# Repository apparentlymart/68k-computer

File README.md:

This is intended to grow into a homebrew computer design based on the Freescale MC68SEC000 CPU.

However, it doesn't do anything yet.

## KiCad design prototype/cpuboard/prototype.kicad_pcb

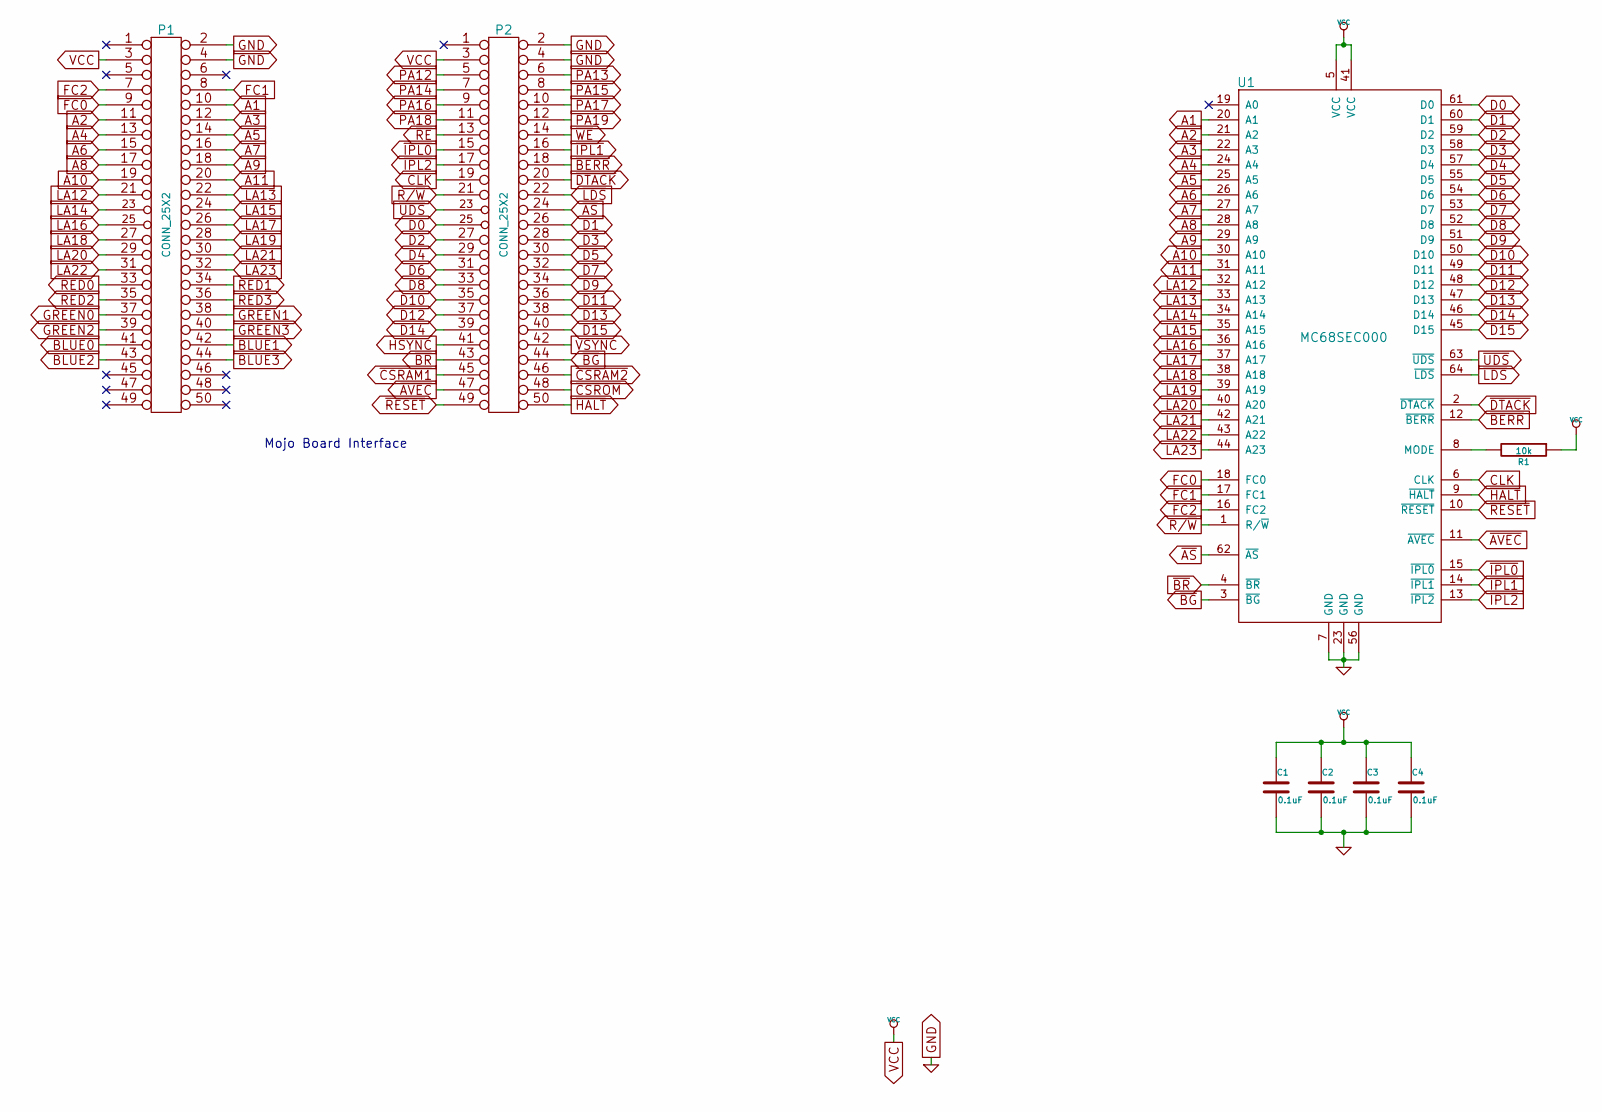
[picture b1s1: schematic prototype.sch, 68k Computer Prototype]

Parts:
C1, C2, C3, C4: 0.1uF; C_0805_HandSoldering
P1, P2: CONN_25X2; Pin_Header_Straight_2x25
R1: 10k; R_0805_HandSoldering
U1: MC68SEC000; LQFP-64_14x14mm_Pitch0.8mm

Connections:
A1: P1.10, U1.20 (A1)
A2: P1.11, U1.21 (A2)
A3: P1.12, U1.22 (A3)
A4: P1.13, U1.24 (A4)
A5: P1.14, U1.25 (A5)
A6: P1.15, U1.26 (A6)
A7: P1.16, U1.27 (A7)
A8: P1.17, U1.28 (A8)
A9: P1.18, U1.29 (A9)
A10: P1.19, U1.30 (A10)
A11: P1.20, U1.31 (A11)
BLUE0: P1.41
BLUE1: P1.42
BLUE2: P1.43
BLUE3: P1.44
CLK: P2.19, U1.6 (CLK)
D0: P2.25, U1.61 (D0)
D1: P2.26, U1.60 (D1)
D2: P2.27, U1.59 (D2)
D3: P2.28, U1.58 (D3)
D4: P2.29, U1.57 (D4)
D5: P2.30, U1.55 (D5)
D6: P2.31, U1.54 (D6)
D7: P2.32, U1.53 (D7)
D8: P2.33, U1.52 (D8)
D9: P2.34, U1.51 (D9)
D10: P2.35, U1.50 (D10)
D11: P2.36, U1.49 (D11)
D12: P2.37, U1.48 (D12)
D13: P2.38, U1.47 (D13)
D14: P2.39, U1.46 (D14)
D15: P2.40, U1.45 (D15)
FC0: P1.9, U1.18 (FC0)
FC1: P1.8, U1.17 (FC1)
FC2: P1.7, U1.16 (FC2)
GND: C1.2, C2.2, C3.2, C4.2, P1.2, P1.4, P2.2, P2.4, U1.7 (GND), U1.23 (GND), U1.56 (GND)
GREEN0: P1.37
GREEN1: P1.38
GREEN2: P1.39
GREEN3: P1.40
HSYNC: P2.41
LA12: P1.21, U1.32 (A12)
LA13: P1.22, U1.33 (A13)
LA14: P1.23, U1.34 (A14)
LA15: P1.24, U1.35 (A15)
LA16: P1.25, U1.36 (A16)
LA17: P1.26, U1.37 (A17)
LA18: P1.27, U1.38 (A18)
LA19: P1.28, U1.39 (A19)
LA20: P1.29, U1.40 (A20)
LA21: P1.30, U1.42 (A21)
LA22: P1.31, U1.43 (A22)
LA23: P1.32, U1.44 (A23)
unnamed: R1.2, U1.8 (MODE)
PA12: P2.5
PA13: P2.6
PA14: P2.7
PA15: P2.8
PA16: P2.9
PA17: P2.10
PA18: P2.11
PA19: P2.12
R/~W: P2.21, U1.1 (R/~W)
RED0: P1.33
RED1: P1.34
RED2: P1.35
RED3: P1.36
VCC: C1.1, C2.1, C3.1, C4.1, P1.3, P2.3, R1.1, U1.5 (VCC), U1.41 (VCC)
VSYNC: P2.42
~AS: P2.24, U1.62 (~AS)
~AVEC: P2.47, U1.11 (~AVEC)
~BERR: P2.18, U1.12 (~BERR)
~BG: P2.44, U1.3 (~BG)
~BR: P2.43, U1.4 (~BR)
~CSRAM1: P2.45
~CSRAM2: P2.46
~CSROM: P2.48
~DTACK: P2.20, U1.2 (~DTACK)
~HALT: P2.50, U1.9 (~HALT)
~IPL0: P2.15, U1.15 (~IPL0)
~IPL1: P2.16, U1.14 (~IPL1)
~IPL2: P2.17, U1.13 (~IPL2)
~LDS: P2.22, U1.64 (~LDS)
~RE: P2.13
~RESET: P2.49, U1.10 (~RESET)
~UDS: P2.23, U1.63 (~UDS)
~WE: P2.14

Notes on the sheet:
Mojo Board Interface

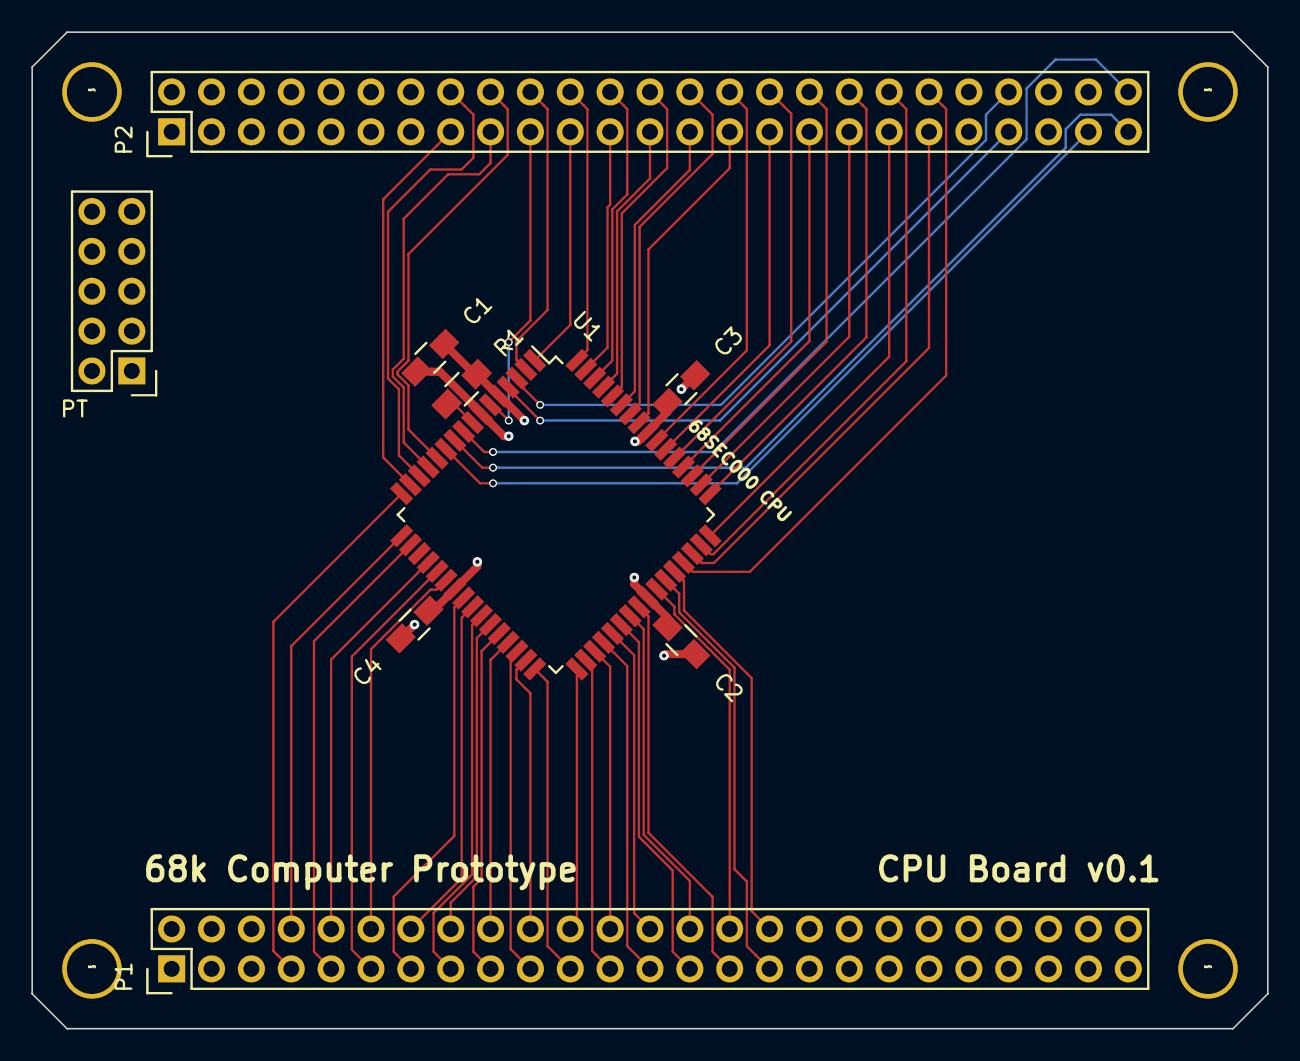
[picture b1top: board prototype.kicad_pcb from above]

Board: 4 copper layers, 78.7 x 63.5 mm, 13 parts (0 on the bottom side), 60 nets.

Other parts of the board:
MNT1, MNT2, MNT3, MNT4: HOLE
PT: Pin_Header_Straight_2x05

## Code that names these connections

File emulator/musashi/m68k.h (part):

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void m68k_modify_timeslice(int cycles); /* Modify cycles left */
void m68k_end_timeslice(void);          /* End timeslice now */

/* Set the IPL0-IPL2 pins on the CPU (IRQ).
 * A transition from < 7 to 7 will cause a non-maskable interrupt (NMI).
 * Setting IRQ to 0 will clear an interrupt request.
 */
void m68k_set_irq(unsigned int int_level);


/* Halt the CPU as if you pulsed the HALT pin. */
void m68k_pulse_halt(void);


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
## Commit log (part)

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2015-01-20 hi
    ____________________________________________________________
    / .--. /\
    / //V\/ _/ /\
    / '--' / \/
    / M C 6 8 0 0 0 /\/
    /___________________________________________________________/ /
2015-01-20 Yosys build script for the glue logic.
2015-01-20 Begin to factor the MMU out into a separate module.
2015-01-25 Simple RAM module to use in test benches.
    (For the real system we will use external RAM.)
2015-01-25 MMU mapping for user mode, via external page table RAM.
2015-01-25 New Makefile target to run Yosys-powered synthesis.
    Will probably want to also support the Xilinx proprietary tools later, but
    open source toolchain is fine for now while we're experimenting.
2015-01-25 Makefile targets to run test benches in Xilinx ISim.
    This is an alternative to using iverilog, which remains the primary way to
    run the test benches.
2015-01-25 Remove redundant begin/end in mmu.
2015-01-25 Show failing tests in prove output.
2015-01-25 Primary I/O Port mapping is actually implemented.
2015-01-25 Map Control, Page Table and Selectable Mappings in supervisor mode.
    This completes the basic MMU functionality.
2015-01-26 Factor out the TAP helpers so they can be used in all testbenches.
2015-02-08 A fake 68000 CPU implementing a 16-bit read cycle.
    This is intended to mock a 68000 CPU so that the memory/peripheral bus
    controller can more easily be tested. Only a 16-bit read cycle is
    implemented so far, but more to come.
2015-02-08 Support the Bus Error signal in fake68k reads.
    Bus Error makes the read cycle two clocks longer and allows the memory
    controller to halt processing until the bus error signal is un-asserted.
    The exception processing that would normally follow a bus error is not
    simulated, since that just entails a pair of standard read cycles to
    obtain the exception handler address.
2015-02-08 Makefile target xilinx_bitstream.
    Produces a bitstream file (.bin file) ready to be uploaded onto a
    Xilinx Spartan6 XC6SLX9 in a TQFP package.
    However, doesn't actually include a physical pin mapping yet so not
    particularly useful. Mainly just blazing the trail of hooking together the
    various Xilinx tools before working on the details of each step.
2015-02-15 Use casex for more readable MMU supervisor address decoding.
2015-03-30 Makefile target for compiling iverilog vpi modules.
    Not used right now, though.
2015-03-30 Local schematic symbol library, with MC68SEC000 symbol.
2015-03-30 Annotate the schematic components.
2015-03-30 VGA connector has mounting hole connections.
2015-03-30 Schematic sheet title.
2015-03-30 Add the flash ROM chip to the prototype schematic.
2015-03-30 Use separate read-enable and write-enable symbols for memory.
    Previously we tried to infer these from a combination of the chip select
    and R/W signals, but that's not possible without additional glue logic so
    we'll just put two more pins on the FPGA output and do the glue logic in
    there instead.
2015-03-30 RAM chip schematic.
2015-03-30 DTACK label should actually be ~DTACK.
2015-03-30 Update parts notes for the prototype board.
2015-04-05 Reassign mojo header pins to move VGA to the other end.
    There is no room at the left-hand edge for the VGA connector because the
    AVR header is in the way, so we need to move it to the right-hand edge.
    To ease routing, the signals should therefore be exposed at that end too.
2015-04-05 Add copper fills to the GND and VCC layers.
2015-04-05 Route the HSYNC and VSYNC signals.
2015-04-05 Route the remaining IC power supplies and decoupling caps.
2015-04-05 Address line traces from Mojo to 68000.
2015-04-05 More 68000 signal traces.
2015-04-05 A tangled mess of traces for physical addresses and one RAM.
    Will probably need to tear all this up and try again.
2015-08-19 "Rescue" the schematic after a KiCad upgrade.
    Some symbols changed in the new version.
2016-01-18 PCB labels
2016-01-18 New top-level module for the prototype
    The prototype is a set of PCBs that stack on top of a Mojo FPGA dev board,
    so the UCF here is mapping to various pins that are exposed on the Mojo
    headers, corresponding to the locations assigned by the prototype PCBs.
2016-01-18 "Free-run" the CPU.
    Free running means that the CPU is just executing no-op instructions over
    and over, incrementing the address bus each time. This is the first
    visible milestone for the project, with some LEDs attached to the top
    8 bits of the address bus showing that it is indeed executing
    instructions.
2016-01-19 Include the memory mapper in the prototype
    For now it's just directly mapping on the top 8 bits of the logical
    address, since we don't have any real memory hardware here anyway and so
    we're just tumbling through memory switching these signals on and off
    but just always returning 0.
2016-01-19 Update memmap testbench for new "physical address strobe" signal
2016-01-19 Valid "no tests" TAP plan for prototype_tb
2016-01-20 Skeleton emulator
    Just as we did for the prototype CPU board, the first step is to
    "free run" the emulated CPU and watch its bus cycles to see if it's
    behaving as expected.
2016-01-20 Initial dummy MMU implementation.
    We don't have the board control registers implemented yet, so we don't
    have a data source for the supervisor map selectors etc. But this does
    mapping of all of the memory spaces that are fixed in supervisor mode.
2016-01-23 Makefile to build a 68k gcc cross-compiler toolchain
2016-01-24 Build a physical ROM image of the OS
    This takes the ELF file produced by building the kernel and extracts the
    relevant segments from it to produce a ROM image that has the segments
    located at the appropriate physical offsets to produce the desired logical
    memory map within the supervisor memory space.
2016-01-25 Various emulator progress
2016-01-25 Trace changes to the MMU control registers
2016-01-25 Target -m68000 and enable debug info
2016-01-25 Unmap the init ROM in assembly
    Previously this was done as the first statement in a C function, but this
    doesn't work because the compiler generates some implied stack
    initalizations which can only be done once the ROM is unselected and the
    RAM revealed in its place.
2016-01-25 Misc progress on kernel and emulator
    Now gets as far as printing a message on the UART.
2016-01-25 Run ten times more CPU cycles per display frame
2016-01-26 Add partial stdint.h header to kernel
    This is just the subset of stdint.h I tend to use regularly. To be extended
    as needed.
2016-01-31 Expose the CPU stopped state in m68k_get_reg
2016-01-31 Optimize the kernel code for size
2016-01-31 As-yet-unused kernel source file
2016-08-08 Pad the program counter to eight digits when disassembling
2016-08-08 Explicitly declare types for rom_size and ram_size.
2016-08-08 Show memory region name in disassembly when tracing instructions
2016-08-08 Mark MMU registers as volatile in the kernel
    Marking them as volatile prevents the compiler from optimizing away writes
    to them, which otherwise it can do because we never read from these
    registers within the kernel code itself.
2016-08-08 Calculate memory device name based on physical address
    Previously we were erroneously using the logical address, giving
    meaningless results.
2016-08-09 Mark the IO base address as volatile
    This address is determined by the linker script and points directly at the
    IO memory space. Marking it as volatile prevents the compiler from
    optimizing away accesses to it, so that reads/writes can have their
    intended I/O side-effects.
2016-08-09 os Makefile target to launch gdb connected to the emulator
2016-08-11 gdbserver supports reading data from memory
    This makes the disassemble and examine commands in gdb work.
2016-08-12 Correct TOOLCHAIN_PATH for the os-toplevel Makefile
2016-08-12 Support single-stepping in the emulator
    This makes the gdb command "step", as well as other commands implemented
    by stepping, work as expected.
2016-08-14 Log when the emulator CPU accesses the exception vector table
    This is useful for debugging when the OS crashes for some reason and we
    don't yet have a specific exception handler installed.
2016-08-14 Generate a tick interrupt every 200ms in the emulator
    This will be our scheduler's timeslice signal, allowing it to preempt a
    user process.
    Since we don't yet have the real interrupt controller designed, and thus
    can't emulate that design, for now we just assume that the timeslice
    signal will be priority 1 and that it will vector to user interrupt vector
    64, which gives us something to hook the OS up to for now, pending some
2016-08-14 More default exception handlers in the kernel.
    We now have at least a generic handler on every vector, rather than having
    some exceptions jump to the beginning of the vector table and start
    trying to execute it.
2016-08-14 Activate the scheduler timeslice in the kernel
    Right now this is entirely academic since there's nothing to schedule, but
    it does demonstrate that the interrupt is working as expected.
2016-08-14 Emulator to do gfx RAM read relative to VRAM, not RAM
    This was a typo that caused crashes when reading from some video RAM
    addresses.
2016-08-14 Need to define the topaz symbol as _topaz so it'll line up with the header
2016-08-15 Consider assembler files when deciding whether to rebuild the kernel
2016-08-15 Drop kernel.c in favor of kernel.s
    The kernel stuff will be low-level enough that it is better written in
    assembly.
2016-08-15 Clean up our exception handling a bit
    The hand-written exception handlers in main.c were getting a bit heavy
    and disorganized. Instead, we'll do the initial bit of exception handling
    in assembly and just delegate to a single C function to deal with the
    "unhandled exception" case.
    This means that for the moment we actually lose our helpful specific
    exception messages. These will probably return later, since we have
2016-08-29 Schematic symbol for a backplane socket
    These are actually PCI sockets physically, but with a custom pinout that
    is tailored to the signals we need for this computer and its peripherals.
2016-09-03 Connect the JTAG data path in the backplane
2016-09-03 AS, LDS and UDS for the CPU and Glue Logic sockets
2017-11-12 os: for now, just stop the CPU when we are ready to schedule
    The scheduler isn't yet functional, so this makes it easier to test the
    emulator itself and make sure it's behaving.
2017-11-12 emulator: use a more accurate cycle-based emulation style
    Previously this was handled in a rather lazy way because we'd not yet
    figured out how the display clock and CPU clock would interact, what
    other interrupts would be present, etc.
    Now that we're starting to solidify the specification of the machine, it's
    better to match a little better the "real" timing behavior, so we can
    start to introduce timer interrupts properly, etc.
2017-12-05 Generate m68k-kiteos- aliases for the cross toolchain
    This will be useful when building user-mode stuff later.
2017-12-05 os/libc: further (failed) attempts to make libc build
2019-09-29 video: Start of video controller; just pixel clock for the moment
    Here we use a PLL block to multiply the 12MHz clock on the ICEbreaker
    board I'm currently using for development to create a 74.25MHz pixel clock
    for 720p video output.
    However, we're not yet generating any other signals, so for the moment
    this is useless and just puts a sine wave on one of our pins.
2019-09-30 video: Use synchronous reset
    Async reset isn't really necessary here, so this makes things a little
    simpler.
2019-10-02 video: Use in-spec parameters for the PLL
    98 is too large for DIVF. Although the PLL did seem to accept it and
    generate approximately the right frequency, the result was too jittery
    to use as a pixel clock.
    We're no longer able to exactly match the target frequency, but this
    frequency of 73.5 MHz, when stable, seems to be accepted by at least the
    one monitor I'm using for testing right now.
2019-10-04 video: Generate clock twice as fast as pixel clock
    We don't have a need for this yet, but since we can do it without
    affecting the pixel clock rate we'll do this and then have a faster clock
    to use for operations that don't need to synchronize with the video
    output, such as blitting.
2019-10-13 video: More fiddling with mouse pointer drawing
    Still not right, but a little closer.

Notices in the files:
emulator/musashi/m68k.h:
Copyright 1998-2001 Karl Stenerud.  All rights reserved.
